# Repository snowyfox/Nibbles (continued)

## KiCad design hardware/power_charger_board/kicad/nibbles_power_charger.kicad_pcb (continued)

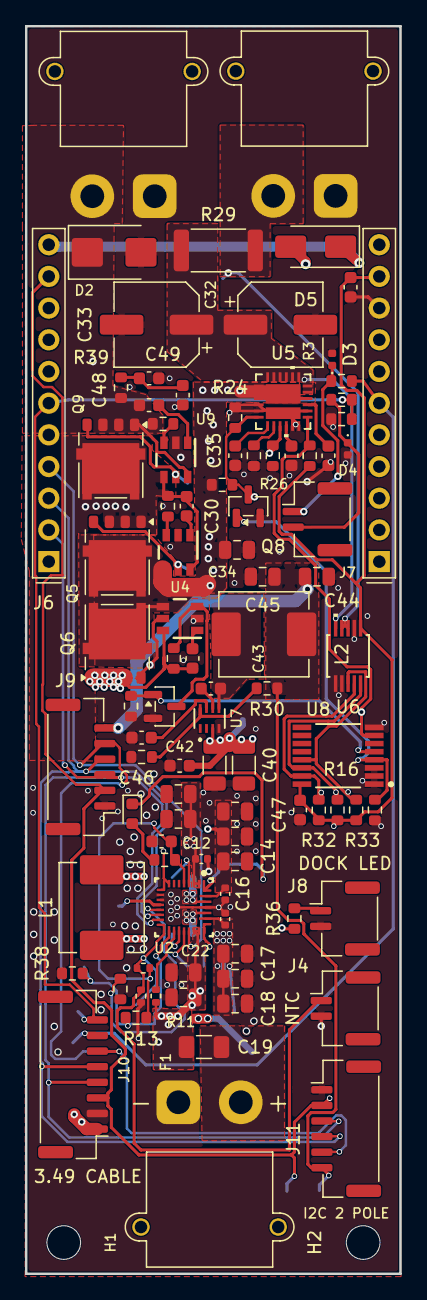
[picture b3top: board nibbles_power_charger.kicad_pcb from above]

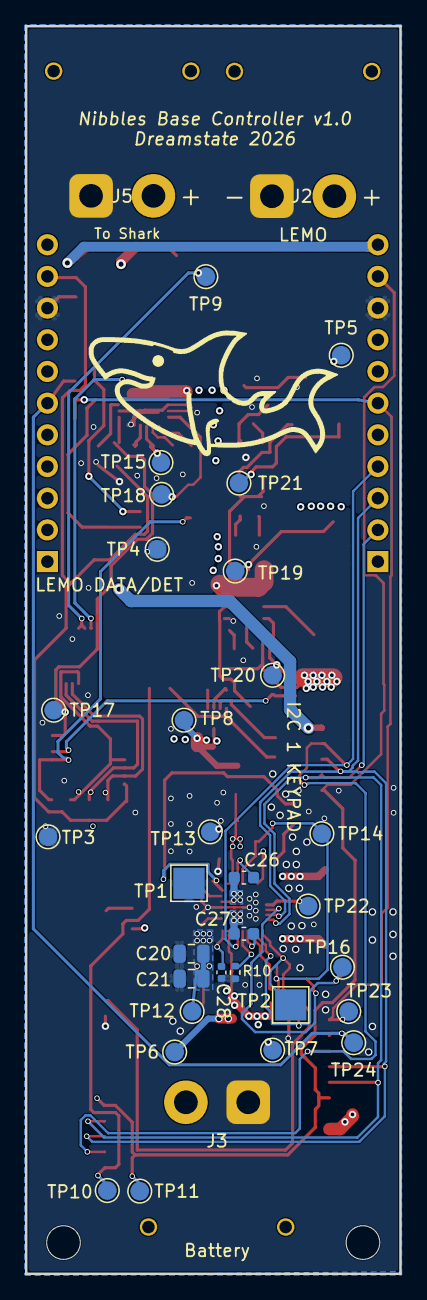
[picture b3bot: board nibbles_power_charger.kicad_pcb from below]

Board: 4 copper layers, 30.0 x 100.0 mm, 126 parts (31 on the bottom side), 58 nets.

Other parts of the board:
H1, H2: M2.5; MountingHole_2.7mm_M2.5
LOGO: Nibbles_Shark_Logo_20mm

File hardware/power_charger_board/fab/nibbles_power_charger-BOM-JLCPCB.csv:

Comment,Designator,Footprint,LCSC Part #
10uF 25V,"C10,C11,C13,C14,C15,C17,C18,C19,C20,C21,C23,C24,C34",C_0805_2012Metric,C15850
0.1uF 25V,"C12,C16,C22",C_0402_1005Metric,C131394
4.7uF 10V,C25,C_0603_1608Metric,C19666
47nF 25V,"C26,C27,C37",C_0603_1608Metric,C1622
1nF 50V,C28,C_0402_1005Metric,C106205
0.1uF,"C30,C31,C38,C42,C43,C47,C48",C_0603_1608Metric,C14663
220uF 25V polymer,"C32,C33",CP_Elec_6.3x9.9,C2981459
22nF,"C35,C36",C_0603_1608Metric,C21122
10uF 35V,"C40,C41",C_1206_3216Metric,C89632
22uF 10V,"C44,C45",C_0805_2012Metric,C45783
10nF,C46,C_0603_1608Metric,C1589
1uF 50V,"C49,C50",C_0603_1608Metric,C15849
SMBJ18A,D2,D_SMB,C10212
TPD1E10B06DPYR,"D3,D4",D_0402_1005Metric,C48260
SS34,D5,D_SMA,C8678
15A,F1,Fuse_1206_3216Metric,C2443310
"XT30PW-M (dock power, from the LEMO)","J2,J3,J5",AMASS_XT30PW-M_1x02_P2.50mm_Horizontal,C431092
"NTC 103AT on the cells (JST-GH 2, vertical)","J4,J7,J8",JST_GH_BM02B-GHS-TBT_1x02-1MP_P1.25mm_Vertical,C161690
To the 3.49 (stacked headers),J6,Waveshare_ESP32-S3-Touch-LCD-3.49_Headers,C2932674
JST-GH 6 vertical (keypad port: I2C),"J9,J11",JST_GH_BM06B-GHS-TBT_1x06-1MP_P1.25mm_Vertical,C189892
"JST-GH 8 vertical (cable to the 3.49, instead of J6)",J10,JST_GH_BM08B-GHS-TBT_1x08-1MP_P1.25mm_Vertical,C133062
2.2uH Isat>=7A,L1,L_Sunlord_MWSA0603S,C285810
6.8uH Isat>=4A,L2,L_Sunlord_MWSA0603S,C285805
LED (charging),LED1,LED_0603_1608Metric,C2286
30V N-FET >= 15 A,"Q5,Q6,Q9",ONSemi_SO-8FL_488AA,C179623
2N7002,"Q7,Q8",SOT-23,C8545
1k,"R3,R4,R27",R_0603_1608Metric,C21190
100k,"R5,R22,R25",R_0603_1608Metric,C25803
27.0k 1%,R10,R_0402_1005Metric,C25771
100,R11,R_0402_1005Metric,C25076
5.23k 1%,R12,R_0402_1005Metric,C2933105
30.1k 1%,R13,R_0402_1005Metric,C2998131
10k,"R14,R16,R24,R28,R31,R37",R_0603_1608Metric,C98220
2.2k,R15,R_0603_1608Metric,C4190
1M,"R20,R21,R35",R_0603_1608Metric,C22935
86.6k 1%,R23,R_0603_1608Metric,C23121
130 1%,R26,R_0603_1608Metric,C22796
2 mOhm 2512 3W,R29,R_2512_6332Metric,C154685
52.3k 1%,R30,R_0603_1608Metric,C2933235
4.7k,"R32,R33",R_0603_1608Metric,C23162
7.5k,R36,R_0603_1608Metric,C23234
10.7k 1%,R38,R_0603_1608Metric,C22857
2 (input snubber),R39,R_0603_1608Metric,C22977
BQ25798RQMR,U2,RQM0029A-MFG,C2876593
LM74700-Q1 (dock),"U3,U4,U9",DBV0006A_N,C2941042
TPS259827ONRGET,U5,RGE24_2P5XP85X1P45_TEX,C2155765
INA226AIDGSR,U6,VSSOP10_DGS_TEX,C49851
TPS62933DRLR,U7,SOT_33DRLR_TEX,C3200405
TCA9534PWR,U8,PW0016A-MFG,C783615

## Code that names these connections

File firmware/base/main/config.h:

// Base station settings. Today this is a prototype on a Waveshare
// ESP32-S3-Touch-LCD-3.49; see docs/architecture.md (Phases 2, 4, 5).
#pragma once

#define BASE_FW_BUILD        2

// 1: always anchor the radio channel. 0: scan for WLED's anchor like the eyes
// (with the fallback below).
#define BASE_IS_ANCHOR       0
// Scanning base: if no anchor (a brain) is heard for this long, the base
// leads a search for one, starting at BASE_ANCHOR_CHANNEL; the eyes and the
// preview screen search with it (NL_HB_GROUP, 2026-11-09).
#define BASE_ANCHOR_FALLBACK_MS 12000
#define BASE_ANCHOR_CHANNEL  6

// Site survey page: listen this long on each channel; recommend only channels
// 1..BASE_MAX_CHANNEL (11: the US); a move happens this long after the tap.
#define SURVEY_DWELL_MS      300
#define BASE_MAX_CHANNEL     11
#define MOVE_DELAY_MS        1000

// Buttons (active low): BOOT = next eye preset; the second key is a bump
// button: the eyes and WLED flash while it is held. The touch screen's FLASH
// and BLACKOUT pads bump the same targets.
#define BTN_NEXT_GPIO        0
#define BTN_BUMP_TARGET      (NL_TARGET_EYES | NL_TARGET_WLED)  // who the bump key flashes
#define BTN_BUMP_GPIO        16

// ---------------------------------------------------------------- mirror board
// A second 3.49 up the pole shows the base's screen and gets its firmware
// from this board over a cable (mirror_link.c, 2026-11-02). Same firmware;
// "role mirror" over USB makes a board the mirror. The main board's end is
// off until "mirror link on" (it takes GPIO 0, the BOOT key, and GPIO 4).
// The 3.49 has no spare header pin free of parts: GPIO 0 has C58 (100 nF,
// the BOOT key's) and GPIO 4 has C10 (100 nF, the battery ADC's) to ground,
// which round a fast signal off. Remove both on the main board for 1 Mbaud
// (or drop MIRROR_BAUD to 19200, slow for updates: ~15 min).
#define MIRROR_UART          1
#define MIRROR_BAUD          1000000
#define MIRROR_MAIN_TX_GPIO  0      // main board: to the mirror's RX (header A1)
#define MIRROR_MAIN_RX_GPIO  4      // main board: from the mirror's TX (header A5)
#define MIRROR_SIDE_TX_GPIO  43     // mirror board: to the main's RX (header B5)
#define MIRROR_SIDE_RX_GPIO  44     // mirror board: from the main's TX (header B6)
#define MIRROR_HELLO_MS      2000   // the main asks the mirror for its build this often

// Status screen: LV_DISPLAY_ROTATION_0 or _180 = portrait (cards stacked),
// _90 or _270 = landscape (cards side by side); each pair picks which way up.
#define DISPLAY_ROTATION     LV_DISPLAY_ROTATION_0
#define DISPLAY_BACKLIGHT_PCT 80

#define CMD_TRIES            3
#define CMD_TIMEOUT_MS       60
#define TAKE_FADE_MS         0       // two brains: LATCH on a held TAKE is a cut; a fade would need a separate key

// ---------------------------------------------------------------- power board
// Its own I2C bus on the 3.49's header (J6 A2-A4 on the power board), dock
// detect on A6. 100 kHz: the keypads share the bus, one of them 60-80 cm away.
#define PIN_PWR_SDA          1
#define PIN_PWR_SCL          2
#define PIN_PWR_INT          3
#define PIN_DOCK_DET         5

// The TF card, in 1-bit SD mode (Waveshare's schematic and factory demo).
#define PIN_SD_CLK           41
#define PIN_SD_CMD           39
#define PIN_SD_D0            40

// The PCF85063 clock (with the board's IMU and other sensors, which we don't use).
#define PIN_RTC_SDA          47
#define PIN_RTC_SCL          48
#define POWER_I2C_HZ         100000
#define POWER_POLL_MS        200
#define BASE_LOAD_MW         2000    // the base itself, for the runtime estimate (estimate)

// Charger (BQ25798) settings, written at start-up and read back (charging is
// switched off if they don't stick). 4S at 4.2 V per cell; 2.0 A is the
// Vapcell F63's standard charge. CHG_IINDPM_MA 0 keeps the input limit the
// board's ILIM_HIZ divider sets (2.0 A, so lights plus charging stay inside
// a VB99 D-Tap's 10 A); a value (100-3300) replaces it.
#define CHG_VREG_MV          16800
#define CHG_ICHG_MA          2000
#define CHG_IINDPM_MA        0

// How often the base tells WLED the pack voltage and the lights' current
// (NL_MSG_BATTERY, for its battery-aware current limit). Simulated readings are never sent.
#define BATTERY_BROADCAST_MS 200

// ---------------------------------------------------------------- keypad
// Key boards on the power board's bus (TCA9534A, address set by each board's
// jumpers) in the order their LEDs are chained (hub J2, J3, ...). Each lists
// its switches top to bottom (switch 1 = P0 = its first LED); KEY_NONE for
// a switch with no job. See controls.h for what the keys do.
// The last entry is the breadboard prototype: a PCF8574T module (no LEDs;
// switches between a pin and GND, its pins pull themselves up) at 0x27, all
// three address jumpers high (PCF8574T: 0x20-0x27; PCF8574AT: 0x38-0x3F).
// A board that isn't there is just never found, so the entries can stay.
#define KEYPAD_BOARDS { \
    { 0x38, KEYPAD_TCA9534, 8, { KEY_NUM1, KEY_NUM2, KEY_NUM3, KEY_NUM4, KEY_NUM5, KEY_NUM6, KEY_NUM7, KEY_NUM8 } }, \
    { 0x39, KEYPAD_TCA9534, 8, { KEY_ALL, KEY_BODY, KEY_EYES, KEY_FINS, KEY_PAGE, KEY_LATCH, KEY_BLACKOUT, KEY_FIN_SENSOR } }, \
    { 0x3A, KEYPAD_TCA9534, 3, { KEY_TAKE, KEY_FLASH, KEY_UNLOCK } }, \
    { 0x27, KEYPAD_PCF8574, 8, { KEY_NUM1, KEY_NUM2, KEY_NUM3, KEY_NUM4, KEY_EYES, KEY_BODY, KEY_LATCH, KEY_TAKE } }, \
}
#define KEYPAD_POLL_MS       10
// The key LEDs' data: GPIO 43 (U0TXD; the console is on USB), wired to the
// hub's J1 pin 7. The ROM prints its boot banner on this pin, so the LEDs
// may flicker for a moment at power-up until the firmware sets them.
#define PIN_KEY_LEDS         43
// Scale for the key LEDs (0-255): 19 SK6812s at full white would draw ~1.1 A
// from the keypad cable's 5 V; 48 keeps it under ~0.25 A and is plenty at night.
#define KEYPAD_LED_LEVEL     48
// Lock the keypad after this long without a key press (0: only by holding UNLOCK).
#define KEYPAD_AUTOLOCK_MS   0

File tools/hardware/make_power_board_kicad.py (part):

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nibbles_ti.pretty, which isn't committed). nibbles.pretty holds the CH224K's
ESSOP-10, drawn here; this board doesn't use it (its only power input is the
LEMO), but the USB-C to LEMO charging dongle will. Every net uses global
labels, so net names are plain (DOCK_VIN, not /Inputs/DOCK_VIN) in both the
schematic and the board.
"""
import json
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# Charger board: the BQ25798 cluster, relative to U2 (pins 25-29
# SYS/SW2/GND/SW1/PMID face up), after the datasheet's layout priorities
# (8.4.1) and Figure 8-21: 0402s from PMID and SYS to GND right at those
# pins with a 10 uF beside each, the rest of PMID's caps on the left and
# SYS's on the right, the inductor just above (SW1/SW2 reach it through vias
# under the IC, on In2), the VBUS 0402 and REGN cap at the left pins, BAT
# caps at the right pins, the slow parts below. Input on the left edge,
# battery on the right, I2C and the NTC on the bottom.
U2_AT = (27.0, 14.5)
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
